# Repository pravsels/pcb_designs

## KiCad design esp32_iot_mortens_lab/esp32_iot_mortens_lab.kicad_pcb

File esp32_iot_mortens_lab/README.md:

# ESP32 IOT Device 

The board is a general IoT device based on an ESP32 WROOM module.

The following features must be integrated:

- Si7021 - I2C temperature and humidity sensor
- QWIIC connector for other I2C devices
- CP2104 - USB 2 serial UART and on board programmer for the ESP32
- RGB LED and a button
- Interface for LED strips, 4 level converted outputs and fused powersupply available on screw terminals
- Power relay
- 3.2mm mouting holes in each corner

The board will measure 80x80mm and it will be a 4 layer board design

## USB-C to UART subcircuit

- USB-C input 
- USBLC6-2P6 for ESD (electro-static discharge) protection 
- CPI2104 for USB to UART conversion 

### USB-C device pins 

- VBUS & GND → Power and ground.
- D+ & D- → USB 2.0 data transfer.
- CC1 & CC2 → Orientation detection & role negotiation.
- SBU1 & SBU2 → Used for alternate modes like DisplayPort.

### USBLC and CP Background 

What is USBLC?

USBLC refers to USB Line Protection Components, specifically USB ESD protection diodes. 
These components are used to protect USB data lines (D+ and D-) from electrostatic discharge (ESD), voltage spikes, and electromagnetic interference (EMI).

How USBLC Works: 

    - The diodes inside the USBLC component act as voltage clamps, preventing voltage spikes from damaging sensitive electronics.
    - They redirect excessive voltage surges (e.g., static electricity from plugging in a USB cable) away from the USB data lines and safely discharge them to ground.
    - This prevents damage to USB transceivers like the CP2104.
    - The USBLC6-2P6 in the circuit is a 6-line ESD protection device, designed to handle fast transient voltage surges.

Why Are USB Data Lines Protected ?

USB ports are externally exposed, making them vulnerable to electrostatic discharge (ESD), voltage spikes, and RF noise. 
Without protection, several issues may arise:

    - ESD discharge (up to ±15kV) can instantly destroy a USB transceiver.
    - Voltage spikes from hot-plugging can cause glitches, corrupted data, or permanent damage.
    - Electromagnetic interference (EMI) can introduce noise and distort USB communication.
    - Using USBLC ensures stable and reliable data transfer while protecting the circuit.

What is CP2104 ?

CP2104 belongs to the CP210x series, a USB-to-UART bridge IC family developed by Silicon Labs.

How CP2104 Works: 

    - Converts USB data (D+ and D-) into UART signals (TX, RX).
    - Enables a USB host (e.g., a PC) to communicate with microcontrollers or embedded systems via serial UART.

Why do we need pull-down resistors for the CC pins ? 

In USB-C, the CC pin is used for detection. The USB host (computer or charger) applies voltage to CC, 
and the device (your circuit) is supposed to pull it down slightly with a 5.1kΩ resistor.

| **Case**                            | **Voltage on CC Pin** | **What the USB Host Thinks**            |
|-------------------------------------|-----------------------|-----------------------------------------|
| ✅ **Correct: 5.1kΩ pull-down**     | ~0.6V                 | "USB 2.0 device attached"               |
| ❌ **No resistor (floating CC)**    | Unknown / unstable    | Device may not be detected              |
| ❌ **Direct connection to GND**     | 0V                    | Host may think there's a short circuit  |

Without a Resistor:

    - The CC pin could pick up noise, making the voltage random and unstable.
    - The USB host won't detect the device properly because it expects a specific voltage drop caused by the 5.1kΩ resistor.
    - The USB host might not enable power or data transfer because it doesn't detect a valid connection.

### Inductor and Fuse Background 

1. Inductor (FB1 - Ferrite Bead)

🔹 Component: BLM21PG221 (Ferrite Bead)

🔹 Purpose: Filters high-frequency noise (EMI suppression)

Why It’s Needed

    - USB power (VBUS) carries noise from chargers, PCs, and RF sources (Wi-Fi, Bluetooth).
    - A ferrite bead acts as a low-pass filter, allowing DC power while blocking high-frequency noise.
    - Prevents EMI from affecting USB signals and internal components.

How It Works

    - Placed in series with +5VP, so all power passes through it first.
    - DC power flows normally, but high-frequency noise is blocked.
    - Improves signal integrity, reducing interference in the CP2104 and other circuits.

2. Fuse (F2 - Polyfuse 1A)

🔹 Component: Polyfuse 1A (Resettable Fuse)

🔹 Purpose: Protects against overcurrent and short circuits

Why It’s Needed

    - USB power has current limits—excess draw can damage components.
    - A short circuit could cause dangerous current spikes.
    - The fuse limits current to 1A and disconnects power if exceeded.

How It Works

    - Placed in series with VBUS (+5V).
    - Normal operation: Passes power if current is < 1A.
    - Overcurrent event (e.g., short circuit): Cuts power if >1A, preventing damage.
    - Auto-resetting: Unlike regular fuses, it recovers when cooled down.

### Capacitors 

Why we need capacitors 

- Stabilize voltage: prevent sudden drops or spikes that can reset or disturb ICs.
- Filter noise: clean up high-frequency and low-frequency noise from USB power (VBUS).
- Ensure reliable USB communication: avoid data errors caused by unstable voltage.

| **Capacitor** | **Value**  | **Purpose**                                                               | **Why It's Needed (Reasoning)**                                                                                                                               |
|---------------|------------|---------------------------------------------------------------------------|---------------------------------------------------------------------------------------------------------------------------------------------------------------|
| **C4**        | 22 µF      | **Bulk decoupling** for low-frequency noise and large voltage swings.     | Smooths out **slow** changes in USB VBUS, handles large current draws (e.g., device startup).                                                                 |
| **C3**        | 4.7 µF     | **Mid-frequency filtering** for medium-speed noise.                       | Absorbs **medium-speed** disturbances that bulk cap (C4) is too slow for, and small cap (C2) can't handle.                                                    |
| **C2**        | 100 nF     | **High-frequency decoupling** for fast noise and transients.              | Filters **high-frequency noise** caused by CP2104's **fast internal switching** (USB traffic, UART activity), provides quick bursts of current when needed.   |

### CP2104 Important Pins and Their Functions

| **Pin**  | **Function**                  | **What You Connect**                                       | **Required** |
|----------|--------------------------------|------------------------------------------------------------|-------------|
| **RST**  | Resets the chip (Active-Low)   | **Pull-up resistor (4.7kΩ - 10kΩ)**                         | ✅ Yes, otherwise random resets may happen. |
| **VDD**  | Main Power Supply              | **100nF + 1µF capacitor**                                   | ✅ Yes, provides power to CP2104. |
| **VIO**  | Sets logic level for I/O pins  | **Tie to 3.3V (or system voltage), add 100nF capacitor**   | ✅ Yes, must match the system logic voltage. |
| **VPP**  | Factory programming voltage    | **Usually leave unconnected**                              | ❌ No, unless you're programming the chip. |

### Power Distribution in the CP2104 Circuit

| **Power Label** | **Voltage**        | **Source**                               | **Used For**       |
|-----------------|--------------------|------------------------------------------|--------------------|
| **+5VP**        | 5V (Raw USB Power) | USB Connector (J5)                       | Direct USB Power (before filtering) |
| **+5V**         | 5V (Filtered)      | After Ferrite Bead (FB1) & Polyfuse (F2) | Powering components, feeding 3.3V regulator. |
| **+3.3VA**      | 3.3V (Regulated)   | From Regulator (CP2104 or external)      | Powering CP2104 and any other 3.3V devices.  |

Why is it Called Analog (+3.3VA)?

In mixed-signal circuits (where digital and analog components coexist), we often separate their power supplies to reduce noise. 
The "A" in +3.3VA stands for Analog, meaning this power rail is meant for sensitive components that need a cleaner voltage supply.

### Difference Between Analog and Digital Power

| **Type**          | **Characteristics**                                      | **Where It's Used?**                          |
|-------------------|---------------------------------------------------------|-----------------------------------------------|
| **Digital Power** | Supplies **logic circuits** that operate in **discrete steps** (1s and 0s). | Microcontrollers, CPUs, UART, GPIO.           |
| **Analog Power**  | Supplies **sensitive circuits** that handle **continuous signals**. | Sensors, ADCs, USB transceivers, RF circuits. |

How Does This Apply to Our Circuit?

    - The CP2104 handles USB signals, which involve continuous waveforms (analog behavior).
    - If digital noise contaminates the USB transceiver power, it can cause bad signal quality or data errors.
    - So, "Analog" power (+3.3VA) is labeled separately to indicate that this voltage should be as clean as possible.

What Happens If You Use the Same 3.3V for Everything?

    - Digital circuits (GPIO, UART) create noise due to fast switching (MHz speeds).
    - USB transceivers (analog part of CP2104) are sensitive to noise.

    - If you use the same power line, USB signal quality may degrade, causing:
        - USB disconnection issues.
        - Increased bit errors in data transfer.
        - EMI (Electromagnetic Interference) problems.

### UART Communication Pins

| **Pin** | **Name**  | **Direction** | **Function**                                               |
|--------|-----------|-------------|------------------------------------------------------------|
| 21     | **TXD**   | Output      | UART Transmit Data (Data sent from CP2104).                |
| 20     | **RXD**   | Input       | UART Receive Data (Data received by CP2104).               |
| 19     | **RTS**   | Output      | Request to Send (Flow control, optional).                  |
| 18     | **CTS**   | Input       | Clear to Send (Flow control, optional).                    |
| 22     | **DSR**   | Input       | Data Set Ready (Handshake signal, often unused).           |
| 23     | **DTR**   | Output      | Data Terminal Ready (Handshake signal, often unused).      |
| 24     | **DCD**   | Input       | Data Carrier Detect (Detects an active serial connection). |
| 1      | **RI**    | Input       | Ring Indicator (For modems, rarely used in standard UART). |

### GPIO and Special Function Pins

| **Pin**  | **Name**          | **Function**                                                         |
|----------|-------------------|----------------------------------------------------------------------|
| 17       | **SUSPEND**       | Active HIGH when USB is suspended. Can be used to power down external circuits. |
| 15       | **SUSPEND**       | Active LOW during USB suspend (opposite logic of pin 17).           |
| 14       | **TXT / GPIO.0**   | Can be used as **GPIO 0** or **Transmitter Enable** for RS485 mode. |
| 13       | **RXT / GPIO.1**   | Can be used as **GPIO 1** or **Receiver Enable** for RS485 mode.    |
| 12       | **RS485 / GPIO.2** | Can be used as **GPIO 2** or **RS485 Direction Control**.           |
| 11       | **GPIO.3**         | General-purpose I/O pin (user-defined function).                    |

### ⚡ General Guideline: Which Components Need Analog Power?
| **Component Type**        | **Power Type** | **Why?** |
|--------------------------|--------------|----------|
| **DACs (Digital-to-Analog Converters)** | **Analog (AVDD)** | Outputs a **continuous signal** that must be clean and low-noise. |
| **ADCs (Analog-to-Digital Converters)** | **Analog (AVDD)** | Converts weak analog signals into digital data, so noise can distort accuracy. |
| **Op-Amps & Analog Signal Amplifiers** | **Analog (AVDD)** | Small voltage fluctuations can cause errors, so a **low-noise** power supply is needed. |
| **Precision Voltage References** | **Analog (AVDD)** | Any noise in the power affects accuracy of **DACs, ADCs, and sensors**. |
| **RF Circuits (WiFi, Bluetooth, etc.)** | **Analog (AVDD)** | Radio signals are highly sensitive to noise from switching power supplies. |
| **Sensors (e.g., temperature, pressure, light sensors)** | **Analog (AVDD)** | Sensor output voltages are often weak, so noise from digital circuits can corrupt them. |

### 🔌 Which Components Can Use Digital Power?
| **Component Type**      | **Power Type** | **Why?** |
|------------------------|--------------|----------|
| **Microcontrollers (MCUs, CPUs, GPUs)** | **Digital (VDD, DVDD)** | Only handle **1s and 0s**, so noise isn’t a big issue. |
| **Digital Logic ICs (AND, OR, Flip-Flops, etc.)** | **Digital (VDD)** | Works with binary signals that tolerate noise. |
| **Flash Memory, RAM, ROM** | **Digital (VDD)** | Purely digital storage, immune to small voltage noise. |
| **UART, SPI, I2C Communication Interfaces** | **Digital (VDD)** | These protocols use high/low logic levels and are designed to handle small noise margins. |
| **LEDs & Display Drivers** | **Digital (VDD)** | LEDs and screens are not affected by minor power fluctuations. |

## RTS/DTR sub-circuit 

- RTS (Request To Send) and DTR (Data Terminal Ready) signals generated by a USB-to-serial interface 
    (such as CP2104) control two digital transistors (UMH3N), labeled as Q1A and Q1B.

- When activated, these transistors pull the microcontroller's IO0 and EN pins LOW, automating the 
    reset sequence and enabling entry into programming mode.

**Signal flow:**
PC → CP2104 (USB-to-UART) → RTS/DTR → Q1A/Q1B transistors → IO0/EN (Microcontroller)

**The proper sequence for programming mode is:**

    - Pull IO0 LOW (by setting RTS LOW).

    - Briefly pull EN LOW (by setting DTR LOW), then release (back HIGH).

After this sequence, if the microcontroller detects IO0 LOW at reset, it enters the programming mode 
(also known as "bootloader mode").

**What is Programming Mode?**

Programming mode (bootloader mode) is a special boot state in microcontrollers that allows you to load new firmware via serial communication (UART). While in this mode, the chip waits for firmware uploads from external tools like the Arduino IDE, ESP flashing tool, or esptool.py.

    - Normal Operation Mode: Microcontroller runs user firmware.

    - Programming (Bootloader) Mode: Microcontroller waits to receive new firmware.

## Relay control sub-circuit 

This sub-circuit is designed to switch a relay on and off using a transistor controlled by a low-voltage input (e.g., from a microcontroller).

### Circuit Components

#### Relay (K1 - RT314A05)

Coil Pins: A1 (+5V), A2 (controlled by transistor)

#### Contacts:

- Pin 11: Common (COM)

- Pin 12: Normally Closed (NC)

- Pin 14: Normally Open (NO)

#### Transistor (Q2 - BC817)

Acts as a low-side switch.

#### Pins:

- 1 (Base): Receives control signal (RELAY input).

- 2 (Emitter): Ground

- 3 (Collector): Connected to relay coil

#### Resistors

R15 (1kΩ): Limits base current into transistor.

R14 (10kΩ): Pull-down resistor, ensures transistor stays off by default.

#### Diode (D1 - LL4148)

Flyback diode, protects transistor from voltage spikes when relay coil turns off.

#### LED Indicator (D2 - Yellow) and Resistor (R16 - 1kΩ)

Indicates when the relay coil is energized.

#### Screw Terminal (J2)

External connections for relay contacts.

### 🔌 Relay Operation
| **Component Type**    | **Power Type** | **Why?**                                           |
|-----------------------|----------------|----------------------------------------------------|
| **Input (RELAY HIGH)**| **Relay ON**   | Relay energized, connects Pin 11 → Pin 14 (NO).    |
| **Input (RELAY LOW)** | **Relay OFF**  | Relay de-energized, connects Pin 11 → Pin 12 (NC). |

**How does high and low inputs activate different circuits?**

HIGH input (RELAY pin):

    - Current flows into transistor base (Q2) → turns transistor ON.

    - Current from +5V passes through relay coil (K1) → energizes relay.

    - Relay contacts move from default position (Pin 11 → Pin 12) to energized position (Pin 11 → Pin 14), activating the connected NO circuit.

    - LED (D2) lights up, indicating the relay is active.

LOW input:

    - No current at transistor base → transistor OFF.

    - Relay coil is not energized → relay contacts return to default (Pin 11 → Pin 12), activating NC circuit.

    - LED turns off.

## 74AHCT245 bi-directional tranceiver sub-circuit 

It receives digital signals from LEDSTR1-4, buffers them using the 74AHCT245 and sends them through 22Ω resistors 
to an 8-pin screw terminal (J3), likely for connecting LED strips. 

subcircuit components: 

🔹 U5: 74AHCT245 - Octal Bus Transceiver

    - Buffers 8 digital signals, here only using 4 (A0 - A3 to B0 - B3) 
    - Direction is fixed A → B (pin 1 DIR is tied to GND).
    - Output Enable (CE pin 19) is pulled LOW (enabled). 
    - Operates on +5V (pin 20) with GND on pin 10.

🔹 Inputs: LEDSTR1-4 (Pins 2-5)

    - These go into A0-A3 and are forwarded to B0-B3 by the transceiver.

🔹 Outputs: B0-B3 (Pins 18-15)

    - Buffered versions of inputs. 
    - Each output goes through a 22Ω resistor (R17-R20) to J3 (Pins 2-5).

🔹 J3: 8-Pin Screw Terminal

    - Outputs to the external world.
    - Pins 2-5 carry signals for LED strips. 
    - Pins 1 and 6-8 are GND or unused (GND is explicitly provided on pin 7). 

🔹 Power Supply:

    - Supplied via screw terminal J4 (pins 1: +5V, 2: GND). 
    - Passes through a fuse (F1) for protection.
    - C1 (1000μF) provides bulk decoupling for inrush when LEDs power up.
    - C14 (100nF) is a local decoupling cap for the IC, handling high-frequency noise.

**What's the output enable pin ?** 

It's a control pin on devices like the 74AHCT245 that determines whether the outputs are active or disabled.

In the tranceiver, Pin 19 (CE) is the Output Enable. It's tied to GND, so it's enabled all the time (i.e., outputs are always active).

**Why do we need buffered versions of input signals ?** 

- Microcontrollers can only supply a few milliamps. Buffer chips can supply more current — especially useful when driving long wires or LEDs.

- The buffer cleans up edges (transitions from LOW to HIGH) and ensures strong digital levels. Prevents voltage drop, ringing, or signal degradation on long traces.

- Some buffers support shifting logic levels (e.g., 3.3V logic to 5V signals). Allows 3.3V MCU to control 5V logic devices. 

**What's the meaning of cleaning up edges ?**

When a digital signal switches from LOW (0V) to HIGH (e.g., 3.3V or 5V), it should happen quickly and sharply.

But:

    - Microcontrollers or long traces might create slow or noisy transitions (not a clean square wave).

    - This can cause unreliable behavior in fast digital circuits.

✅ What the buffer does:

    - It takes that sloppy or weak input signal and re-drives it with a clean, sharp edge — fast rise/fall times, full logic levels.

    - Ensures the output is a strong, reliable digital HIGH or LOW.

## Overview of the whole schematic 

### Power & Programming Interface 

The USB port delivers 5V and provides serial communication via a USB-to-UART bridge, 
which includes ESD protection on the data lines. Auto-boot signals (RTS/DTR) allow the 
ESP32 to enter bootloader mode for hands-free programming. 

### 5V to 3.3V LDO 

A linear regulator drops the USB 5V supply to 3.3V for the ESP32 and peripherals, with 
decoupling capacitors to ensure stable operation. An LED on the 3.3V rail indicates when 
power is active. 

Note: 'decoupling' implies that the capacitors isolate a device's local power demands from the larger supply rails. By acting as a local energy reservoir, a decoupling capacitor reduces how 
much sudden current draws or noise in one part of the circuit can affect others. 

### ESP32 Module 

A WiFi/Bluetooth enabled ESP32 module, featuring recommended pull-ups, pull-downs and 
capacitors on its strapping pins, forms the core of the design. The auto-boot circuitry 
ties into EN and IO0 to simplify firmware flashing. 

### I2C (Qwiic/STEMMA QT)

A dedicated connector offers a 3.3V I2C interface for easily adding sensors and modules. 
An on-board temperature/humidity sensor resides on the same bus, making use of the same 
pull-up resistors. 

### LED Driver 

A 74AHCT245 IC level-shifts the 3.3V signals from the ESP32 to 5V logic, buffering 4 data 
lines that exit via JST-style connectors for driving external LED strips or modules. 

### Relay 

A transistor based driver energizes the relay coil under ESP32 control, with a flyback diode 
preventing voltage spikes during switch offs. The relay's contacts are exposed for switching external loads at higher voltages and currents. 

### User I/O 

Push buttons for RESET, BOOT or general purpose use, provide direct user interaction. Status LEDs offer visible feedback for various functions. 

### Mounting 

Mounting holes at the corners allow secure attachment to an enclosure or chassis. Keep-out 
areas around these holes ensure that standoffs or screws won't interfere with nearby components.

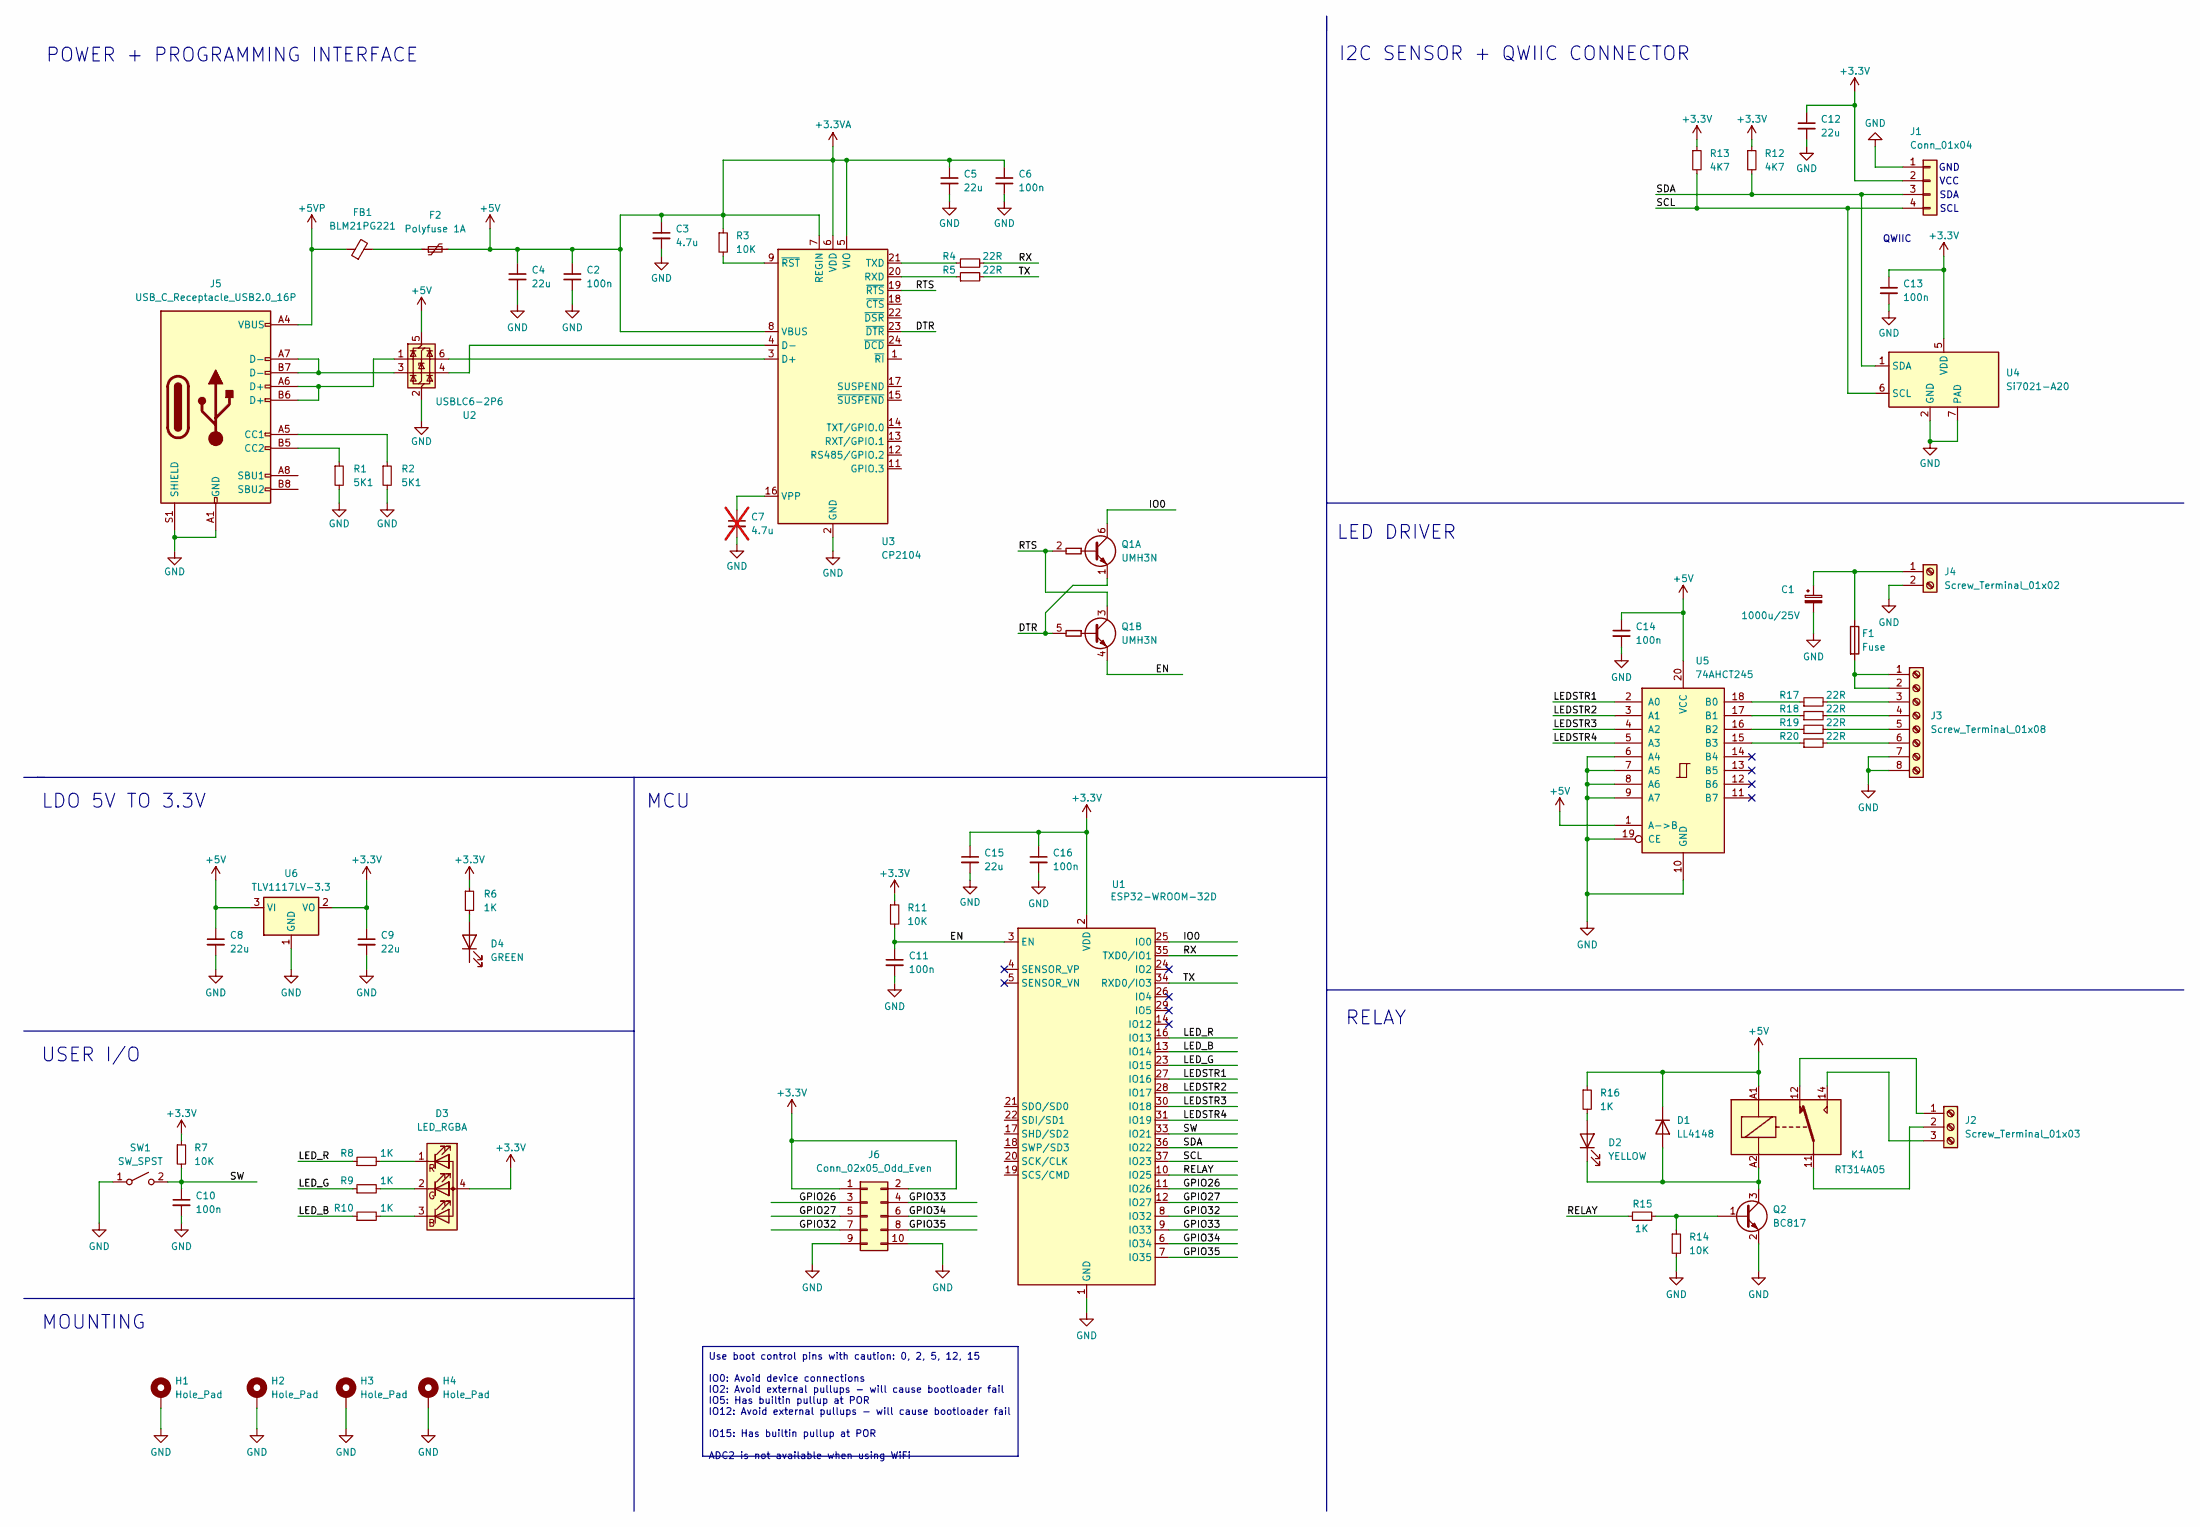
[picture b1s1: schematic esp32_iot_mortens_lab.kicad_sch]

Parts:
C1: 1000u/25V; CP_Radial_D10.0mm_P5.00mm
C2, C6, C10, C11, C13, C14, C16: 100n; C_0402_1005Metric_Pad0.74x0.62mm_HandSolder
C3: 4.7u; C_0805_2012Metric_Pad1.18x1.45mm_HandSolder
C4, C5, C8, C9, C12, C15: 22u; C_0805_2012Metric_Pad1.18x1.45mm_HandSolder
C7: 4.7u; C_0805_2012Metric_Pad1.18x1.45mm_HandSolder; not fitted
D1: LL4148; D_MiniMELF
D2: YELLOW; LED_0603_1608Metric_Pad1.05x0.95mm_HandSolder
D3: LED_RGBA; LED_RGB_Wuerth-PLCC4_3.2x2.8mm_150141M173100
D4: GREEN; LED_0603_1608Metric_Pad1.05x0.95mm_HandSolder
F1: Fuse; FUSE_696105003002
F2: Polyfuse 1A; Fuse_1206_3216Metric_Pad1.42x1.75mm_HandSolder
FB1: BLM21PG221; L_0603_1608Metric_Pad1.05x0.95mm_HandSolder
H1, H2, H3, H4: Hole_Pad; MountingHole_3.2mm_M3_Pad_Via
J1: Conn_01x04; JST_SH_SM04B-SRSS-TB_1x04-1MP_P1.00mm_Horizontal
J2: Screw_Terminal_01x03; TerminalBlock_Phoenix_MKDS-3-3-5.08_1x03_P5.08mm_Horizontal
J3: Screw_Terminal_01x08; TerminalBlock_Phoenix_MKDS-1,5-8_1x08_P5.00mm_Horizontal
J4: Screw_Terminal_01x02; TerminalBlock_Phoenix_MKDS-1,5-2-5.08_1x02_P5.08mm_Horizont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
J5: USB_C_Receptacle_USB2.0_16P; USB_C_Receptacle_HRO_TYPE-C-31-M-12
J6: Conn_02x05_Odd_Even; PinHeader_2x05_P2.54mm_Vertical
K1: RT314A05; Relay_SPDT_Schrack-RT1-16A-FormC_RM5mm
Q1: UMH3N; SOT-363_SC-70-6
Q2: BC817; SOT-23
R1, R2: 5K1; R_0402_1005Metric_Pad0.72x0.64mm_HandSolder
R3, R7, R11, R14: 10K; R_0402_1005Metric_Pad0.72x0.64mm_HandSolder
R4, R5, R17, R18, R19, R20: 22R; R_0402_1005Metric_Pad0.72x0.64mm_HandSolder
R6, R8, R9, R10, R15, R16: 1K; R_0402_1005Metric_Pad0.72x0.64mm_HandSolder
R12, R13: 4K7; R_0402_1005Metric_Pad0.72x0.64mm_HandSolder
SW1: SW_SPST; SW_Push_1P1T_NO_6x6mm_H9.5mm
U1: ESP32-WROOM-32D
U2: USBLC6-2P6; SOT-666
U3: CP2104; QFN-24-1EP_4x4mm_P0.5mm_EP2.6x2.6mm
U4: Si7021-A20; DFN-6-1EP_3x3mm_P1mm_EP1.5x2.4mm
U5: 74AHCT245; DIP-20_W7.62mm
U6: TLV1117LV-3.3; SOT-223-3_TabPin2

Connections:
+3.3V: C9.1, C12.1, C13.1, C15.1, C16.1, D3.4 (A), J1.2, J6.1, J6.2, R6.1, R7.1, R11.1, R12.1, R13.1, U1.2 (VDD), U4.5 (VDD), U6.2 (VO)
+3.3VA: C2.1, C3.1, C4.1, C5.1, C6.1, C8.1, C14.1, D1.1 (K), F2.2, K1.A1, R3.1, R16.1, U2.5 (VBUS), U3.5 (VIO), U3.6 (VDD), U3.7 (REGIN), U3.8 (VBUS), U5.1 (A->B), U5.20 (VCC), U6.3 (VI)
+5VP: FB1.1, J5.A4 (VBUS), J5.A9 (VBUS), J5.B4 (VBUS), J5.B9 (VBUS)
/DTR: Q1.1 (E1), Q1.5 (B2), U3.23 (~DTR)
/EN: C11.1, Q1.4 (E2), R11.2, U1.3 (EN)
/GPIO26: J6.3, U1.11 (IO26)
/GPIO27: J6.5, U1.12 (IO27)
/GPIO32: J6.7, U1.8 (IO32)
/GPIO33: J6.4, U1.9 (IO33)
/GPIO34: J6.6, U1.6 (IO34)
/GPIO35: J6.8, U1.7 (IO35)
/IO0: Q1.6 (C1), U1.25 (IO0)
/LEDSTR1: U1.27 (IO16), U5.2 (A0)
/LEDSTR2: U1.28 (IO17), U5.3 (A1)
/LEDSTR3: U1.30 (IO18), U5.4 (A2)
/LEDSTR4: U1.31 (IO19), U5.5 (A3)
/LED_B: R10.1, U1.13 (IO14)
/LED_G: R9.1, U1.23 (IO15)
/LED_R: R8.1, U1.16 (IO13)
/RELAY: R15.1, U1.10 (IO25)
/RTS: Q1.2 (B1), Q1.3 (C2), U3.19 (~RTS)
/RX: R4.2, U1.35 (TXD0/IO1)
/SCL: J1.4, R13.2, U1.37 (IO23), U4.6 (SCL)
/SDA: J1.3, R12.2, U1.36 (IO22), U4.1 (SDA)
/SW: C10.1, R7.2, SW1.2 (B), U1.33 (IO21)
/TX: R5.2, U1.34 (RXD0/IO3)
GND: C1.2, C2.2, C3.2, C4.2, C5.2, C6.2, C7.2, C8.2, C9.2, C10.2, C11.2, C12.2, C13.2, C14.2, C15.2, C16.2, H1.1, H2.1, H3.1, H4.1, J1.1, J3.7, J3.8, J4.2, J5.A1 (GND), J5.A12 (GND), J5.B1 (GND), J5.B12 (GND), J5.S1 (SHIELD), J6.9, J6.10, Q2.2 (E), R1.2, R2.2, R14.2, SW1.1 (A), U1.1 (GND), U1.15 (GND), U1.38 (GND), U1.39 (GND), U2.2 (GND), U3.2 (GND), U3.25 (GND), U4.2 (GND), U4.7 (PAD), U5.6 (A4), U5.7 (A5), U5.8 (A6), U5.9 (A7), U5.10 (GND), U5.19 (CE), U6.1 (GND)
unnamed: D1.2 (A), D2.1 (K), K1.A2, Q2.3 (C)
unnamed: D2.2 (A), R16.2
unnamed: D3.3 (BK), R10.2
unnamed: D3.2 (GK), R9.2
unnamed: D3.1 (RK), R8.2
unnamed: D4.2 (A), R6.2
unnamed: F2.1, FB1.2
unnamed: J2.1, K1.12
unnamed: J2.2, K1.11
unnamed: J2.3, K1.14
unnamed: F1.2, J3.1, J3.2
unnamed: J3.3, R17.2
unnamed: J3.4, R18.2
unnamed: J3.5, R19.2
unnamed: J3.6, R20.2
unnamed: C1.1, F1.1, J4.1
unnamed: J5.A5 (CC1), R2.1
unnamed: J5.B5 (CC2), R1.1
unnamed: J5.A6 (D+), J5.B6 (D+), U2.1 (I/O1)
unnamed: J5.A7 (D-), J5.B7 (D-), U2.3 (I/O2)
unnamed: Q2.1 (B), R14.1, R15.2
unnamed: U2.6 (I/O1), U3.3 (D+)
unnamed: U2.4 (I/O2), U3.4 (D-)
unnamed: R5.1, U3.20 (RXD)
unnamed: R4.1, U3.21 (TXD)
unnamed: C7.1, U3.16 (VPP)
unnamed: R3.2, U3.9 (~RST)
unnamed: R17.1, U5.18 (B0)
unnamed: R18.1, U5.17 (B1)
unnamed: R19.1, U5.16 (B2)
unnamed: R20.1, U5.15 (B3)

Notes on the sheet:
Use boot control pins with caution: 0, 2, 5, 12, 15 IO0: Avoid device connections IO2: Avoid external pullups - will cause bootloader fail IO5: Has builtin pullup at POR IO12: Avoid external pullups - will cause bootloader fail IO15: Has builtin pullup at POR ADC2 is not available when using WiFi
QWIIC
I2C SENSOR + QWIIC CONNECTOR
SCL
MOUNTING
LDO 5V TO 3.3V
RELAY
VCC
SDA
LED DRIVER
USER I/O
POWER + PROGRAMMING INTERFACE
MCU
GND

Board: 2 copper layers, 63 parts (0 on the bottom side), 58 nets, no tracks yet.

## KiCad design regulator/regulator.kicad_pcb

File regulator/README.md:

# TPS79333-EP Power Regulation Circuit
5V to 3.3V regulator with noise filtering and status indicators.

## Components

### Core
- **U1 (TPS79333-EP)**
  - Regulates 5V input to stable 3.3V output
  - Handles load current changes
  - EN pin enables regulator when powered
  - BP pin for internal reference stability

- **J1, J2 (Conn_01x02)**
  - Simple 2-pin power connectors
  - Handle power in (5V) and out (3.3V)
  - Ground return path for current

### Power Stability
- **C1 (0.1μF)**
  - Smooths input voltage fluctuations
  - Protects regulator from input noise
  - Fast response to high-frequency noise

- **C2 (2.2μF)**
  - Main output stabilization
  - Supplies current during load changes
  - Maintains 3.3V while regulator adjusts
  - Required for regulator stability

- **C3 (0.01μF)**
  - Catches high-frequency output noise
  - Partners with C2 for better stability
  - Fast response to small fluctuations

### Indicators
- **R1 (649Ω) & D1**
  - Shows 5V power is present
  - R1 limits LED current (~5mA)

- **R2 (280Ω) & D2**
  - Shows 3.3V output is working
  - R2 limits LED current (~10mA)

## Usage Notes
- Designed for unstable/noisy power sources
- Can handle varying load currents
- LEDs help with troubleshooting

## Key Concepts

### How Capacitors Work

- Two conductive plates separated by insulator (dielectric)
- When voltage applied, charges separate onto plates
- This separation creates an electric field storing energy

Acts like inertia for voltage:
- If circuit voltage tries to rise: capacitor absorbs charge, fighting the increase
- If circuit voltage tries to drop: capacitor releases charge, fighting the decrease
- This resistance to change helps smooth out fluctuations

### Load Current

"Load" is whatever device you're powering

Devices draw varying amounts of current:
- LEDs: ~20mA (steady)
- Microcontrollers: ~100mA (can spike)
- Motors: several amps (very variable)

C2 maintains 3.3V while regulator adjusts to load changes
- Sudden current changes try to change voltage (V = IR)
- Capacitors resist these voltage changes by releasing/absorbing charge

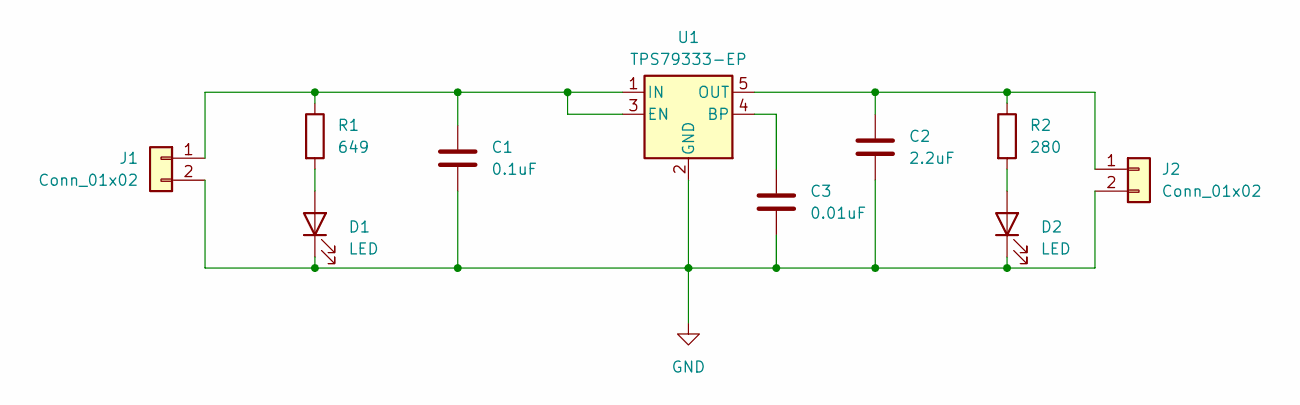
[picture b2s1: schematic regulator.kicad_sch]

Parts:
C1: 0.1uF; C_0805_2012Metric
C2: 2.2uF; C_0805_2012Metric
C3: 0.01uF; C_0805_2012Metric
D1, D2: LED; LED_0805_2012Metric
J1, J2: Conn_01x02; PinHeader_1x02_P2.54mm_Vertical
R1: 649; R_0805_2012Metric
R2: 280; R_0805_2012Metric
U1: TPS79333-EP; SOT-23-5

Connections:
GND: C1.2, C2.2, C3.2, D1.1 (K), D2.1 (K), J1.2, J2.2, U1.2 (GND)
unnamed: D1.2 (A), R1.2
unnamed: D2.2 (A), R2.2
unnamed: C1.1, J1.1, R1.1, U1.1 (IN), U1.3 (EN)
unnamed: C2.1, J2.1, R2.1, U1.5 (OUT)
unnamed: C3.1, U1.4 (BP)

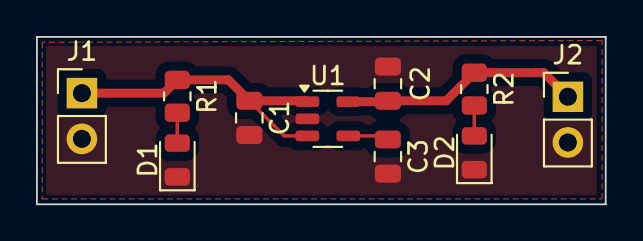
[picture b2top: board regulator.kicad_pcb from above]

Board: 2 copper layers, 31.6 x 9.3 mm, 10 parts (0 on the bottom side), 6 nets.

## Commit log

2025-01-26 regulator schematic
2025-01-27 pcb layout (connection errors)
2025-01-29 readme
2025-01-30 one error
2025-02-24 readmes
2025-02-24 upto USB to UART bridge CP2104
2025-02-25 upto J2 screw
2025-02-26 upto fuse & capacitance
2025-02-28 resistors to cc pins of usb_c
2025-03-03 usb-c to electrostatic discharge device
2025-03-04 readme about USBLC and CP2104
2025-03-05 upto adding power to the usb/uart circuit
2025-03-07 pins 1,6 to D+; pins 3,4 to D- as per GPT and datasheet
2025-03-09 inductor and fuse bg
2025-03-09 added capacitors
2025-03-14 capacitor readme
2025-03-19 upto VDD/VIO/VPP pins
2025-03-20 readme table fixes
2025-03-20 fixed readme table
2025-03-20 analog and digital power tables
2025-03-24 RTS/DTR subcircuit
2025-03-25 upto LDO and LED subcircuits
2025-03-28 qwiic connector
2025-03-30 relay subcircuit
2025-03-31 bi-directional transceiver subcircuit
2025-03-31 tranceiver readme
2025-03-31 transceiver readme fix
2025-04-01 starting to connect esp32
2025-04-02 full schematic done
2025-04-06 overview of the finished schematic
2025-04-08 footprints except for fuse and switch
2025-05-09 got footprints for fuse and button
2025-05-09 adding onju voice
2025-05-10 pcb placement
2025-05-18 phils lab mshd course begin
2025-05-19 lesson 2 usb requirements
2025-05-20 processor reqs
2025-05-21 power supply reqs
2025-05-22 converter reqs
2025-05-23 adc/dac reqs
2025-05-24 misc reqs, op-amp
2025-05-29 lesson 3 part selection basics
